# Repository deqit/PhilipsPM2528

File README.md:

# Reviving a Philips PM2528 Digital Multimeter
Picked up this vintage multimeter a while back. Half-functional, no manuals, and full of mystery. Perfect!

It’s built around an Intel 8035 microcontroller and packed with analog boards. There wasn’t a complete service manual anywhere, so I decided to dive in myself. This project's become a learning experience in hardware reverse engineering, firmware disassembly, and documentation.

Also see https://hackaday.io/project/203720-reviving-a-philips-pm2528-digital-multimeter

# The project
The goal of this project is fixing the multimeter. Well... maybe not really. In real life, the road towards that goal is much more interesting. And I'm documenting everything I found along the way.

In this repository you'll find:
- Original Philips-documentation (at least, what I could find, unfortunately in lo-res)
- Schematics (KiCad)
- PCB Layouts (KiCad)
- Schematic/PCB of a risercard, for testing the expansionboards
- Disassembled firmware, including annotations (Ghidra)
- A lot of documentation regarding relais-mapping, IO-expander-ports, etc.
- Detailed scope- and logic analyzer screenprints and capture-logs
- Deepdive: Explaination of how-everything-works
- etc.

Everything you find here is work-in-progress. It might be incomplete, and some parts may not be 100% accurate yet. If you spot something interesting or catch an error, feel free to drop me a message.

# The components
### Overview
- See [PM2528 Overview](/Deepdive/Overview/README.md "A very broad overview")
### Risercard
- See [PM2528 Risercard](/Deepdive/Risercard/README.md "A Risercard for testing the Expansionboards")
### ADC
- See [ADC Overview](/Deepdive/ADC/README.md "The ADC in more detail")
- See [ADC Control (Expansionboard N20)](/Deepdive/N20/README.md "ADC Control (Expansionboard N20)")
- See [ADC Analog (Expansionboard N21)](/Deepdive/N21/README.md "ADC Analog (Expansionboard N21)")

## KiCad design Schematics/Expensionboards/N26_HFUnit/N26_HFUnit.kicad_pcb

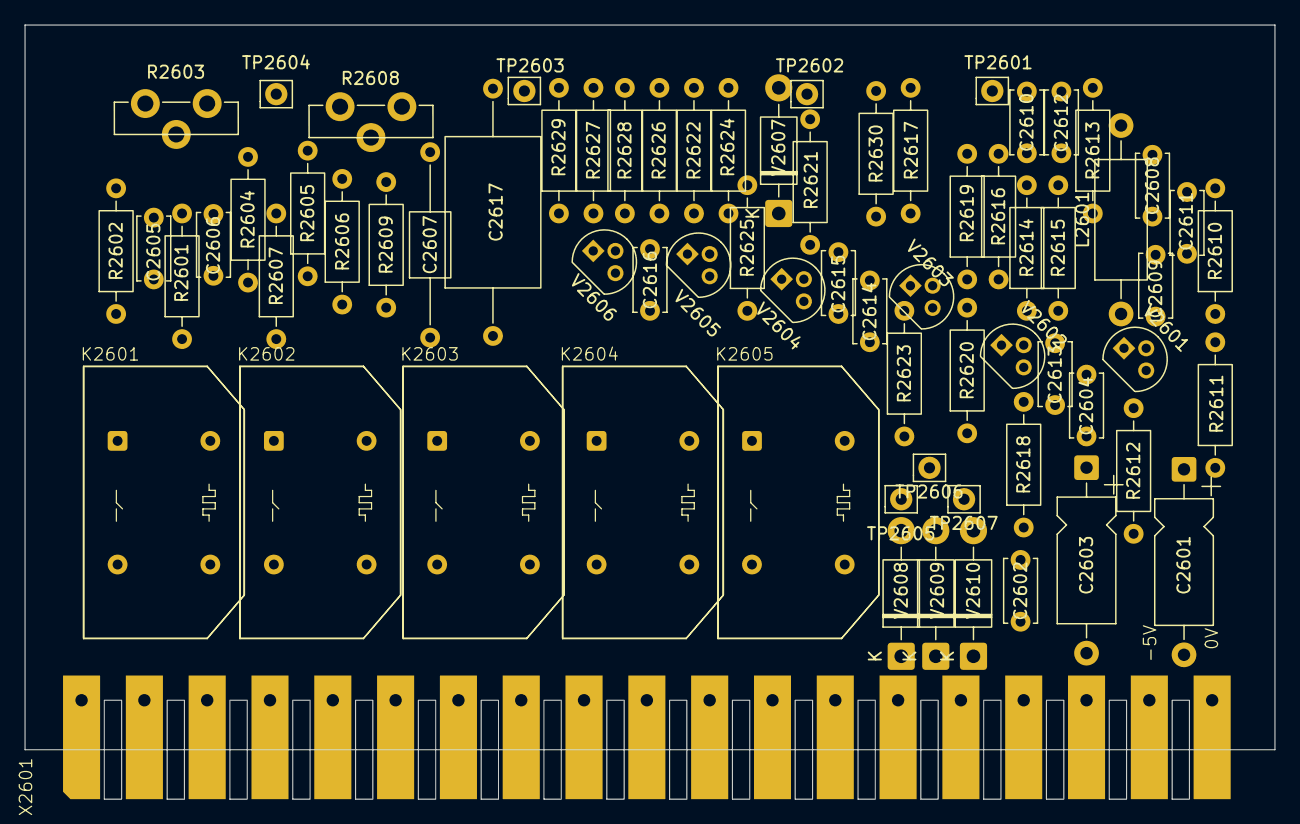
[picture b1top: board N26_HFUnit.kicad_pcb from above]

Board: 2 copper layers, 101.1 x 62.6 mm, 71 parts (0 on the bottom side), 40 nets, no tracks yet.

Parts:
C2601, C2603: 22u; CP_Axial_L10.0mm_D4.5mm_P15.00mm_Horizontal
C2602, C2604, C2610, C2611: 22n; C_Disc_D5.0mm_W2.5mm_P5.00mm
C2605, C2606, C2612, C2614, C2616: 10n; C_Disc_D5.0mm_W2.5mm_P5.00mm
C2607: 4n22; C_Axial_L5.1mm_D3.1mm_P15.00mm_Horizontal
C2608, C2609: 4n7; C_Disc_D5.0mm_W2.5mm_P5.00mm
C2613, C2615: 2n2; C_Disc_D5.0mm_W2.5mm_P5.00mm
C2617: 21n5; C_Axial_L12.0mm_D7.5mm_P20.00mm_Horizontal
K2601, K2602, K2603, K2604, K2605: Reed relay assy
L2601: 1m; L_Axial_L9.5mm_D4.0mm_P15.24mm_Horizontal_Fastron_SMCC
R2601: 4k02; R_Axial_DIN0207_L6.3mm_D2.5mm_P10.16mm_Horizontal
R2602, R2604, R2606: 1M; R_Axial_DIN0207_L6.3mm_D2.5mm_P10.16mm_Horizontal
R2603, R2608: 47k; Trimmer vertical
R2605: 10M; R_Axial_DIN0207_L6.3mm_D2.5mm_P10.16mm_Horizontal
R2607: 100; R_Axial_DIN0207_L6.3mm_D2.5mm_P10.16mm_Horizontal
R2609, R2622: 10k; R_Axial_DIN0207_L6.3mm_D2.5mm_P10.16mm_Horizontal
R2610: 8k25; R_Axial_DIN0207_L6.3mm_D2.5mm_P10.16mm_Horizontal
R2611: 27k4; R_Axial_DIN0207_L6.3mm_D2.5mm_P10.16mm_Horizontal
R2612: 3k83; R_Axial_DIN0207_L6.3mm_D2.5mm_P10.16mm_Horizontal
R2613: 33k2; R_Axial_DIN0207_L6.3mm_D2.5mm_P10.16mm_Horizontal
R2614: 68R1; R_Axial_DIN0207_L6.3mm_D2.5mm_P10.16mm_Horizontal
R2615: 4k64; R_Axial_DIN0207_L6.3mm_D2.5mm_P10.16mm_Horizontal
R2616, R2621: 5k62; R_Axial_DIN0207_L6.3mm_D2.5mm_P10.16mm_Horizontal
R2617: 12k1; R_Axial_DIN0207_L6.3mm_D2.5mm_P10.16mm_Horizontal
R2618, R2620, R2623, R2625, R2626: 15k4; R_Axial_DIN0207_L6.3mm_D2.5mm_P10.16mm_Horizontal
R2619, R2624: 178; R_Axial_DIN0207_L6.3mm_D2.5mm_P10.16mm_Horizontal
R2627, R2629: 154; R_Axial_DIN0207_L6.3mm_D2.5mm_P10.16mm_Horizontal
R2628, R2630: 2k26; R_Axial_DIN0207_L6.3mm_D2.5mm_P10.16mm_Horizontal
TP2601, TP2602, TP2603, TP2604, TP2605, TP2606, TP2607: TestPoint; Pin_D0.9mm_L10.0mm_W2.4mm_FlatFork
V2601, V2602, V2603, V2604, V2605, V2606: BC547B; TO-92
V2607: OA95; D_DO-41_SOD81_P10.16mm_Horizontal
V2608, V2609, V2610: BAX12A; D_DO-41_SOD81_P10.16mm_Horizontal
X2601: PM2528_RiserCardConnector

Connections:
+15V: C2601.1, C2602.1, C2608.1, C2611.1, L2601.1, R2608.3, R2610.2, R2617.2, R2622.2, R2627.2, X2601.4
+Vprobe: C2605.1, R2602.2, X2601.16
-15V: C2603.2, C2604.2, R2608.1, R2618.1, R2620.1, R2623.1, R2625.1, R2628.1, X2601.3
-Vprobe: C2606.2, R2604.1, X2601.15
/DCAmp: K2604.1, X2601.10
/DataholdA: K2603.1, X2601.12
/DataholdB: C2617.1, K2603.5, X2601.13
/LGND3: C2605.2, C2606.1, K2601.5, K2602.1, R2601.1, R2607.1, TP2604.1 (1_1), X2601.18
/LGND4: K2601.6, K2602.6, K2603.6, K2604.6, K2605.6, V2608.1 (K), V2609.1 (K), V2610.1 (K), X2601.19
/LGND5: C2601.2, C2602.2, C2603.1, C2604.1, C2611.2, C2613.1, C2615.1, R2611.1, R2612.1, R2614.1, R2619.1, R2624.1, R2626.1, V2607.1 (K), X2601.1 (0V_1)
/OCAmp: R2630.1, X2601.11
/Probe_0VA: K2602.5, X2601.14
/Probe_0VB: R2601.2, X2601.17
/REL2600A: K2601.10, TP2605.1 (1_1), V2608.2 (A), X2601.9
/REL2600B: K2602.10, K2603.10, TP2606.1 (1_1), V2609.2 (A), X2601.7
/REL2600C: K2604.10, K2605.10, TP2607.1 (1_1), V2610.2 (A), X2601.6
unnamed: C2607.1, R2603.2, R2605.2, R2609.1
unnamed: C2608.2, C2609.1, C2612.2, R2612.2, R2613.2
unnamed: C2609.2, L2601.2
unnamed: C2610.1, R2613.1, R2614.2
unnamed: C2610.2, TP2601.1 (1_1)
unnamed: C2612.1, R2615.2
unnamed: C2613.2, R2616.1
unnamed: C2614.1, R2623.2
unnamed: C2614.2, R2617.1
unnamed: C2615.2, R2621.1
unnamed: C2616.1, R2626.2
unnamed: C2616.2, R2622.1
unnamed: C2617.2, R2629.1, TP2603.1 (1_1)
unnamed: K2601.1, R2602.1, R2603.3
unnamed: K2604.5, R2609.2
unnamed: R2603.1, R2604.2
unnamed: R2605.1, R2606.2, R2607.2
unnamed: R2606.1, R2608.2
unnamed: R2610.1, R2611.2
unnamed: R2615.1, R2618.2
unnamed: R2619.2, R2620.2
unnamed: R2624.2, R2625.2
unnamed: R2628.2, R2629.2
unnamed: C2607.2, R2616.2, R2621.2, R2630.2, TP2602.1 (1_1), V2607.2 (A)

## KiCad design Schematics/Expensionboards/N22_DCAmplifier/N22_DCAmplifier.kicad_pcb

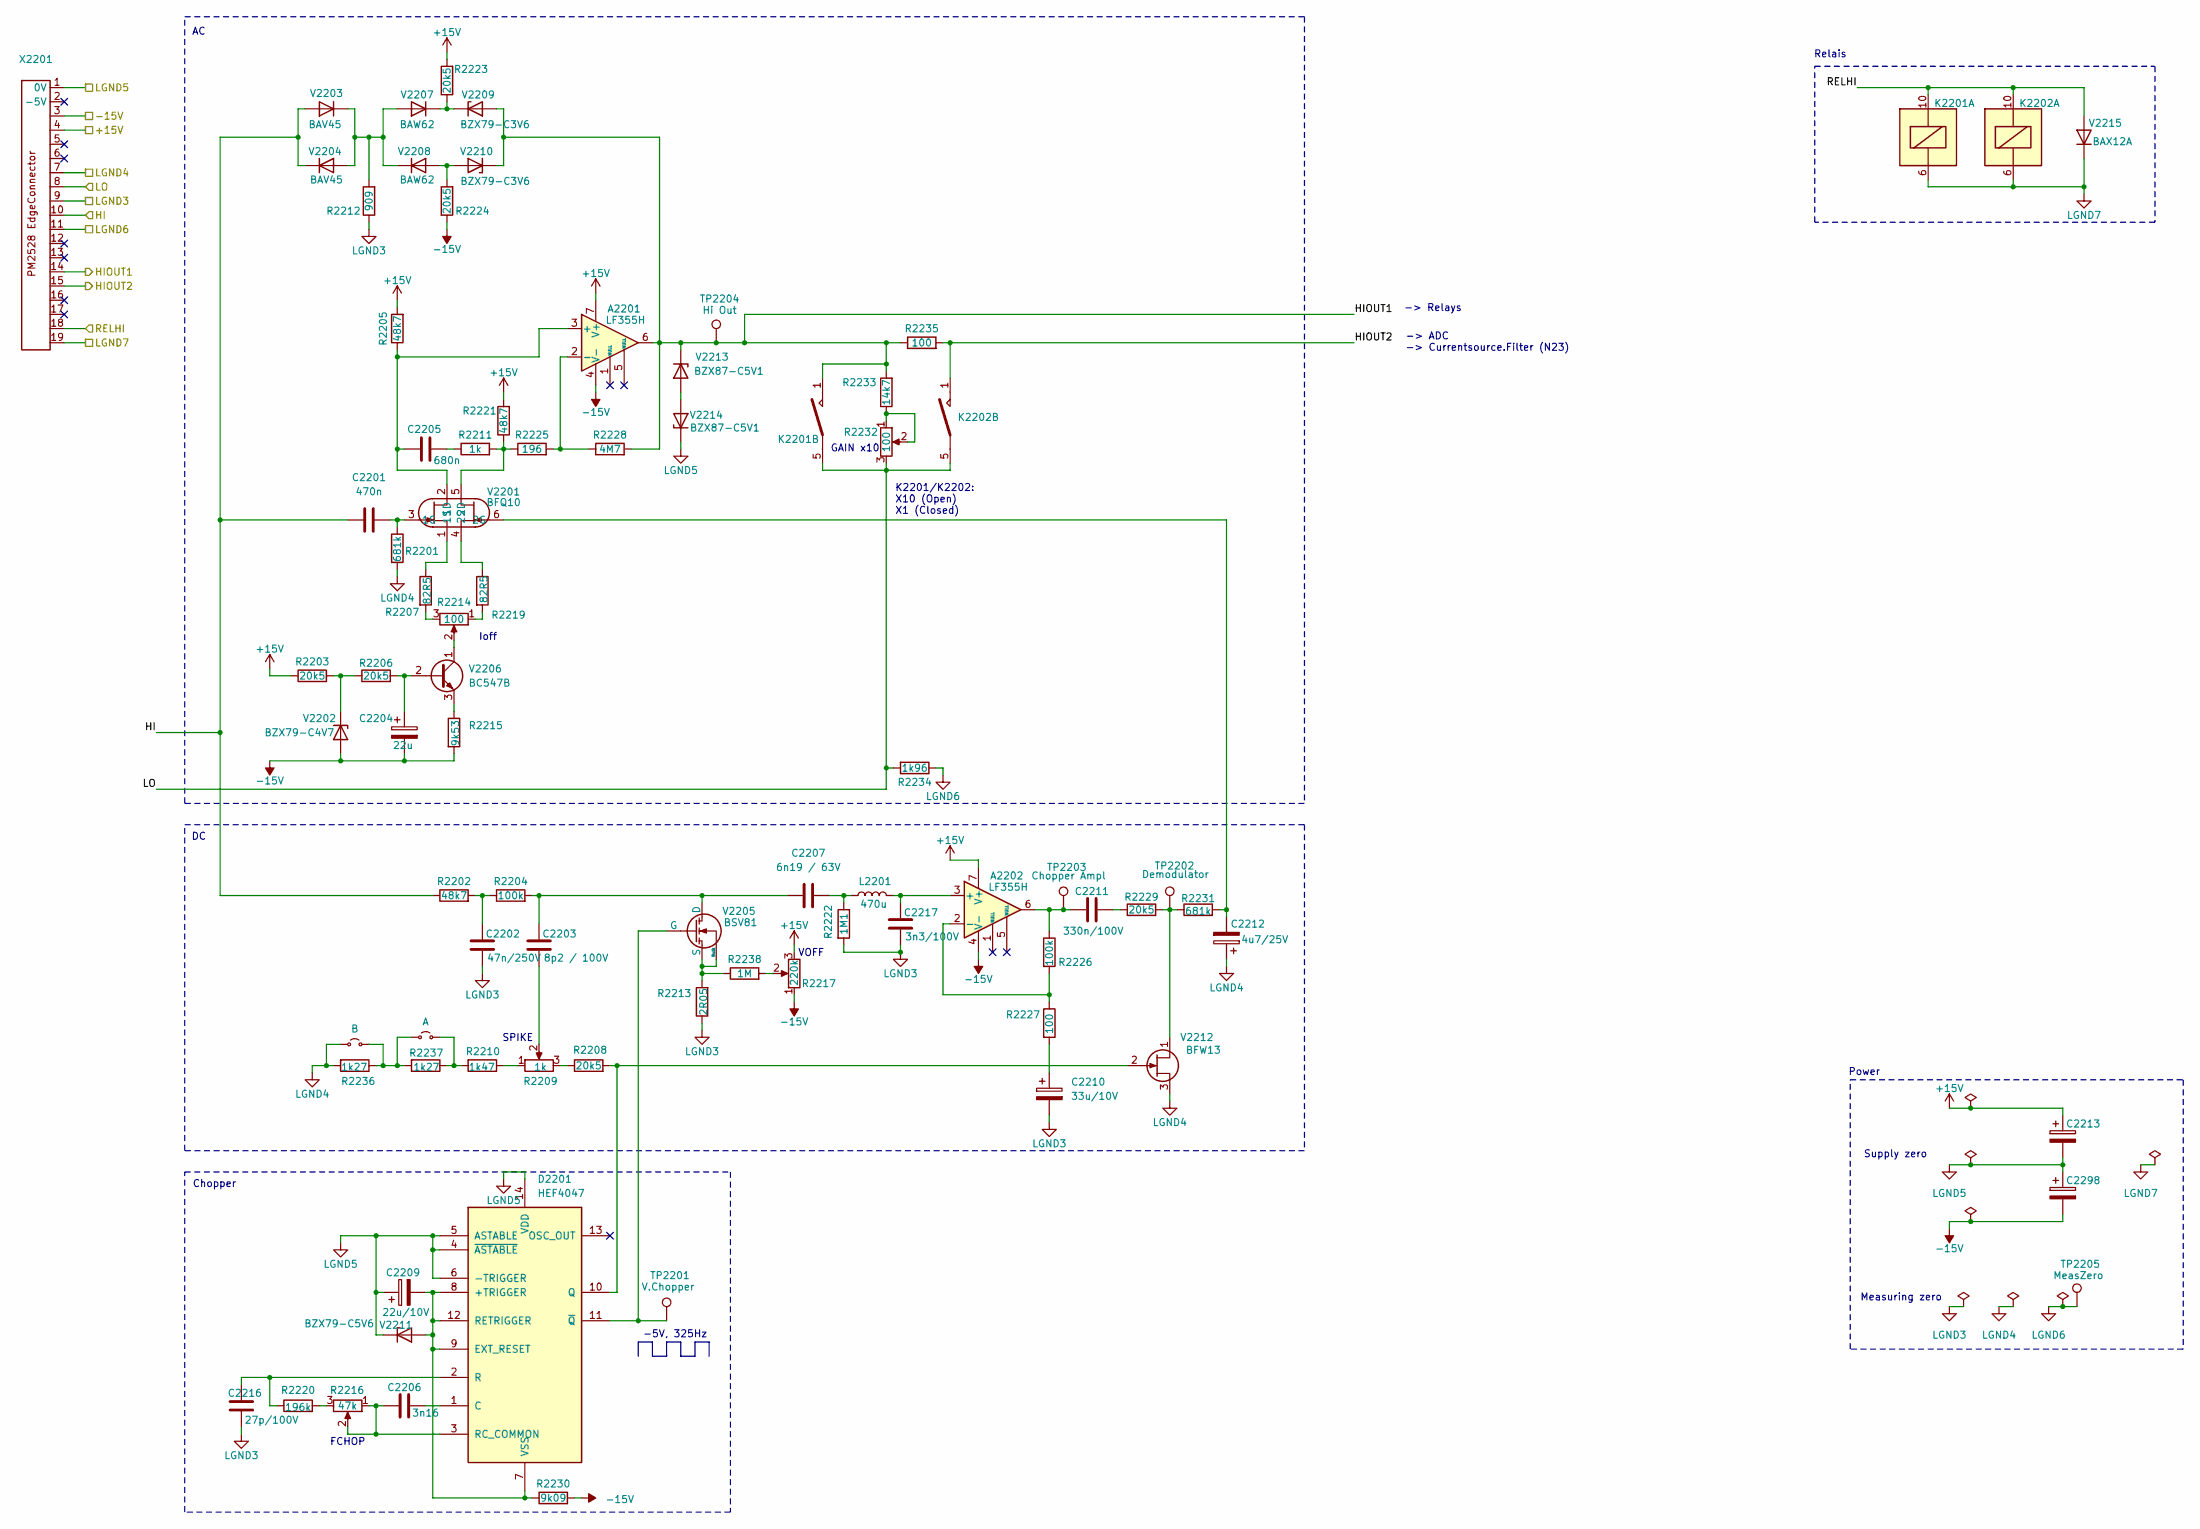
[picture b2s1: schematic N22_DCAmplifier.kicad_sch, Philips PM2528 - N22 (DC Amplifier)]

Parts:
A2201, A2202: LF355H; DIP-8_W7.62mm
C2201: 470n; C_Rect_L18.0mm_W6.0mm_P15.00mm_FKS3_FKP3
C2202: 47n/250V; C_Rect_L10.0mm_W4.0mm_P7.50mm_FKS3_FKP3
C2203: 8p2 / 100V; C_Disc_D4.3mm_W1.9mm_P5.00mm
C2204: 22u; CP_Radial_Tantal_D4.5mm_P5.00mm
C2205: 680n; C_Rect_L18.0mm_W5.0mm_P15.00mm_FKS3_FKP3
C2206: 3n16; C_Axial_L3.8mm_D2.6mm_P15.00mm_Horizontal
C2207: 6n19 / 63V; C_Axial_L3.8mm_D2.6mm_P15.00mm_Horizontal
C2209: 22u/10V; C_Disc_D5.0mm_W2.5mm_P5.00mm
C2210: 33u/10V; CP_Radial_Tantal_D4.5mm_P5.00mm
C2211: 330n/100V; C_Rect_L18.0mm_W5.0mm_P15.00mm_FKS3_FKP3
C2212: 4u7/25V; CP_Radial_Tantal_D4.5mm_P5.00mm
C2213, C2298: C_Polarized; C_Disc_D4.7mm_W2.5mm_P5.00mm
C2216: 27p/100V; C_Disc_D5.1mm_W3.2mm_P5.00mm
C2217: 3n3/100V; C_Disc_D4.3mm_W1.9mm_P5.00mm
D2201: HEF4047; DIP-14_W7.62mm
JP2201: A; TestPoint_Bridge_Pitch5.08mm_Drill0.7mm
JP2202: B; TestPoint_Bridge_Pitch5.08mm_Drill0.7mm
K2201, K2202: Reed relay assy
L2201: 470u; L_Axial_L9.5mm_D4.0mm_P15.24mm_Horizontal_Fastron_SMCC
R2201, R2231: 681k; R_Axial_DIN0207_L6.3mm_D2.5mm_P10.16mm_Horizontal
R2202, R2205, R2221: 48k7; R_Axial_DIN0207_L6.3mm_D2.5mm_P10.16mm_Horizontal
R2203, R2206, R2208, R2223, R2224, R2229: 20k5; R_Axial_DIN0207_L6.3mm_D2.5mm_P10.16mm_Horizontal
R2204, R2226: 100k; R_Axial_DIN0207_L6.3mm_D2.5mm_P10.16mm_Horizontal
R2207, R2219: 82R5; R_Axial_DIN0207_L6.3mm_D2.5mm_P10.16mm_Horizontal
R2209: 1k; Trimmer vertical
R2210: 1k47; R_Axial_DIN0207_L6.3mm_D2.5mm_P10.16mm_Horizontal
R2211: 1k; R_Axial_DIN0207_L6.3mm_D2.5mm_P10.16mm_Horizontal
R2212: 909; R_Axial_DIN0207_L6.3mm_D2.5mm_P10.16mm_Horizontal
R2213: 2R05; R_Axial_DIN0207_L6.3mm_D2.5mm_P10.16mm_Horizontal
R2214, R2232: 100; Trimmer vertical
R2215: 9k53; R_Axial_DIN0207_L6.3mm_D2.5mm_P10.16mm_Horizontal
R2216: 47k; Trimmer vertical
R2217: 220k; Trimmer vertical
R2220: 196k; R_Axial_DIN0207_L6.3mm_D2.5mm_P10.16mm_Horizontal
R2222: 1M1; R_Axial_DIN0207_L6.3mm_D2.5mm_P10.16mm_Horizontal
R2225: 196; R_Axial_DIN0207_L6.3mm_D2.5mm_P10.16mm_Horizontal
R2227, R2235: 100; R_Axial_DIN0207_L6.3mm_D2.5mm_P10.16mm_Horizontal
R2228: 4M7; R_Axial_DIN0207_L6.3mm_D2.5mm_P10.16mm_Horizontal
R2230: 9k09; R_Axial_DIN0207_L6.3mm_D2.5mm_P10.16mm_Horizontal
R2233: 14k7; R_Axial_DIN0207_L6.3mm_D2.5mm_P10.16mm_Horizontal
R2234: 1k96; R_Axial_DIN0207_L6.3mm_D2.5mm_P10.16mm_Horizontal
R2236, R2237: 1k27; R_Axial_DIN0207_L6.3mm_D2.5mm_P10.16mm_Horizontal
R2238: 1M; R_Axial_DIN0309_L9.0mm_D3.2mm_P12.70mm_Horizontal
TP2201: V.Chopper; Pin_D0.9mm_L10.0mm_W2.4mm_FlatFork
TP2202: Demodulator; Pin_D0.9mm_L10.0mm_W2.4mm_FlatFork
TP2203: Chopper Ampl; Pin_D0.9mm_L10.0mm_W2.4mm_FlatFork
TP2204: Hi Out; Pin_D0.9mm_L10.0mm_W2.4mm_FlatFork
TP2205: MeasZero; Pin_D0.9mm_L10.0mm_W2.4mm_FlatFork
V2201: BFQ10; TO-75-6
V2202: BZX79-C4V7; D_DO-35_SOD27_P10.16mm_Horizontal
V2203, V2204: BAV45; D_DO-35_SOD27_P7.62mm_Horizontal
V2205: BSV81; TO-72-4
V2206: BC547B; TO-92_Inline
V2207, V2208: BAW62; D_DO-35_SOD27_P10.16mm_Horizontal
V2209, V2210: BZX79-C3V6; D_DO-35_SOD27_P10.16mm_Horizontal
V2211: BZX79-C5V6; D_DO-35_SOD27_P10.16mm_Horizontal
V2212: BFW13; TO-72-4
V2213, V2214: BZX87-C5V1; D_DO-35_SOD27_P12.70mm_Horizontal
V2215: BAX12A; D_DO-35_SOD27_P10.16mm_Horizontal
X2201: PM2528_RiserCardConnector

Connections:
+15V: A2201.7 (V+), A2202.7 (V+), C2213.1, R2203.1, R2205.2, R2217.3, R2221.2, R2223.2, X2201.4
-15V: A2201.4 (V-), A2202.4 (V-), C2204.2, C2298.2, R2215.2, R2217.1, R2224.1, R2230.2, V2202.2 (A), X2201.3
/HI: C2201.1, R2202.1, V2203.2 (A), V2204.1 (K), X2201.10
/HIOUT1: A2201.6, K2201.1, R2228.2, R2233.2, R2235.1, TP2204.1 (1_1), V2209.2 (A), V2210.1 (K), V2213.1 (K), X2201.14
/HIOUT2: K2202.1, R2235.2, X2201.15
/LGND3: C2202.1, C2210.2, C2216.1, C2217.1, R2212.1, R2213.1, R2222.2, X2201.9
/LGND4: C2212.1, JP2202.1 (A_1), R2201.2, R2236.2, V2212.3 (S), X2201.7
/LGND5: C2209.1, C2213.2, C2298.1, D2201.4 (~ASTABLE), D2201.5 (ASTABLE), D2201.6 (-TRIGGER), D2201.14 (VDD), V2211.1 (K), V2214.1 (K), X2201.1 (0V_1)
/LGND6: R2234.1, TP2205.1 (1_1), X2201.11
/LGND7: K2201.6, K2202.6, V2215.1 (K), X2201.19
/LO: K2201.5, K2202.5, R2232.3, R2234.2, X2201.8
/RELHI: K2201.10, K2202.10, V2215.2 (A), X2201.18
unnamed: A2201.3 (+), C2205.1, R2205.1, V2201.2 (1D)
unnamed: A2201.2 (-), R2225.2, R2228.1
unnamed: A2202.3 (+), C2217.2, L2201.2
unnamed: A2202.2 (-), R2226.2, R2227.1
unnamed: A2202.6, C2211.1, R2226.1, TP2203.1 (1_1)
unnamed: C2202.2, R2202.2, R2204.1
unnamed: C2203.1, R2209.2
unnamed: C2205.2, R2211.1
unnamed: C2207.2, L2201.1, R2222.1
unnamed: C2210.1, R2227.2
unnamed: C2211.2, R2229.1
unnamed: C2209.2, D2201.7 (VSS), D2201.8 (+TRIGGER), D2201.9 (EXT_RESET), D2201.12 (RETRIGGER), R2230.1, V2211.2 (A)
unnamed: C2206.2, D2201.1 (C)
unnamed: D2201.10 (Q), R2208.2, V2212.2 (G)
unnamed: C2216.2, D2201.2 (R), R2220.1
unnamed: C2206.1, D2201.3 (RC_COMMON), R2216.1, R2216.2
unnamed: D2201.11 (~Q), TP2201.1 (1_1), V2205.2 (G)
unnamed: JP2201.1 (A_1), JP2202.2 (B), R2236.1, R2237.2
unnamed: JP2201.2 (B), R2210.2, R2237.1
unnamed: R2207.2, R2214.3
unnamed: R2208.1, R2209.3
unnamed: R2209.1, R2210.1
unnamed: R2214.1, R2219.2
unnamed: R2216.3, R2220.2
unnamed: R2217.2, R2238.2
unnamed: R2232.1, R2232.2, R2233.1
unnamed: C2201.2, R2201.1, V2201.3 (1G)
unnamed: R2207.1, V2201.1 (1S)
unnamed: R2211.2, R2221.1, R2225.1, V2201.5 (2D)
unnamed: C2212.2, R2231.2, V2201.6 (2G)
unnamed: R2219.1, V2201.4 (2S)
unnamed: R2203.2, R2206.1, V2202.1 (K)
unnamed: R2212.2, V2203.1 (K), V2204.2 (A), V2207.2 (A), V2208.1 (K)
unnamed: R2213.2, R2238.1, V2205.3 (S), V2205.4 (Bulk)
unnamed: C2203.2, C2207.1, R2204.2, V2205.1 (D)
unnamed: C2204.1, R2206.2, V2206.2 (B)
unnamed: R2214.2, V2206.1 (C)
unnamed: R2215.1, V2206.3 (E)
unnamed: R2223.1, V2207.1 (K), V2209.1 (K)
unnamed: R2224.2, V2208.2 (A), V2210.2 (A)
unnamed: R2229.2, R2231.1, TP2202.1 (1_1), V2212.1 (D)
unnamed: V2213.2 (A), V2214.2 (A)

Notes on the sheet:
-> Relays
Relais
-> ADC -> Currentsource.Filter (N23)
FCHOP
SPIKE
Supply zero
GAIN x10
K2201/K2202: X10 (Open) X1 (Closed)
VOFF
Chopper
-5V, 325Hz
Power
Measuring zero
Ioff

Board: 2 copper layers, 81 parts (0 on the bottom side), 54 nets, no tracks yet.

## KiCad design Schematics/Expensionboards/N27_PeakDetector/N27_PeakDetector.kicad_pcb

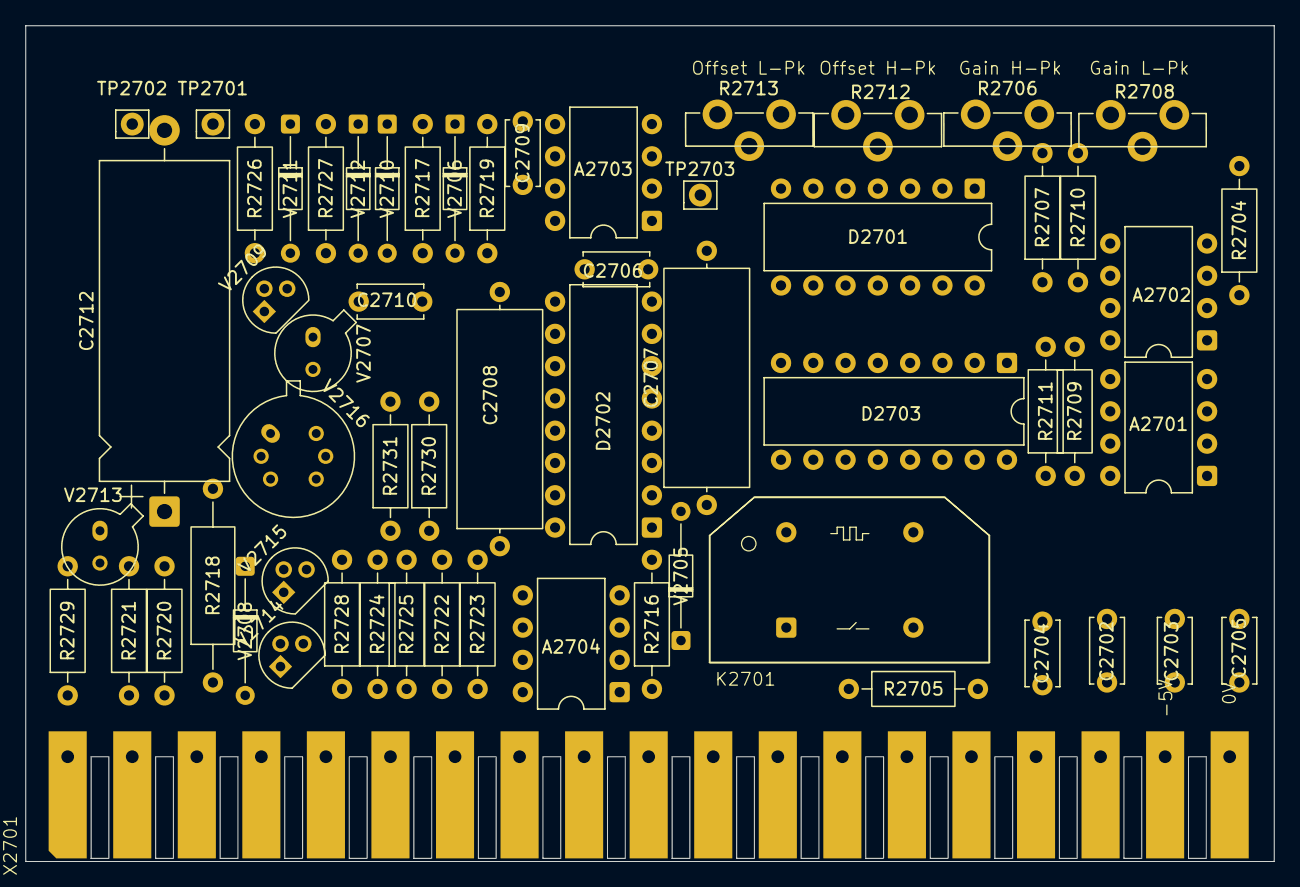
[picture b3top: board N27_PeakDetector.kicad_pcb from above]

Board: 2 copper layers, 98.2 x 65.8 mm, 60 parts (0 on the bottom side), 46 nets, no tracks yet.

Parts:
A2701, A2702, A2704: LF355H; DIP-8_W7.62mm
A2703: LM315; DIP-8_W7.62mm
C2702, C2703: 6u8; C_Disc_D5.0mm_W2.5mm_P5.00mm
C2704, C2705: 22u; C_Disc_D5.0mm_W2.5mm_P5.00mm
C2706, C2709, C2710: 2u2; C_Disc_D5.0mm_W2.5mm_P5.00mm
C2707: 680n; C_Axial_L17.0mm_D6.5mm_P20.00mm_Horizontal
C2708: 220n; C_Axial_L17.0mm_D6.5mm_P20.00mm_Horizontal
C2712: 162n; CP_Axial_L25.0mm_D10.0mm_P30.00mm_Horizontal
D2701: HEF4066; DIP-14_W7.62mm
D2702: HEF4528; DIP-16_W7.62mm
D2703: HEF4104; DIP-16_W7.62mm
K2701: Reed relay assy
R2704: 10k1; R_Axial_DIN0207_L6.3mm_D2.5mm_P10.16mm_Horizontal
R2705: 90k9; R_Axial_DIN0207_L6.3mm_D2.5mm_P10.16mm_Horizontal
R2706: 330; Trimmer vertical
R2707: 36k5; R_Axial_DIN0207_L6.3mm_D2.5mm_P10.16mm_Horizontal
R2708: 100; Trimmer vertical
R2709, R2711: 1k; R_Axial_DIN0207_L6.3mm_D2.5mm_P10.16mm_Horizontal
R2710: 10k; R_Axial_DIN0207_L6.3mm_D2.5mm_P10.16mm_Horizontal
R2712, R2713: 22k; Trimmer vertical
R2716: 1M8; R_Axial_DIN0207_L6.3mm_D2.5mm_P10.16mm_Horizontal
R2717: 1M1; R_Axial_DIN0207_L6.3mm_D2.5mm_P10.16mm_Horizontal
R2718: 33M; R_Axial_DIN0309_L9.0mm_D3.2mm_P15.24mm_Horizontal
R2719: 100k; R_Axial_DIN0207_L6.3mm_D2.5mm_P10.16mm_Horizontal
R2720: 226k; R_Axial_DIN0207_L6.3mm_D2.5mm_P10.16mm_Horizontal
R2721: 287; R_Axial_DIN0207_L6.3mm_D2.5mm_P10.16mm_Horizontal
R2722, R2723: 5k62; R_Axial_DIN0207_L6.3mm_D2.5mm_P10.16mm_Horizontal
R2724, R2730, R2731: 48k7; R_Axial_DIN0207_L6.3mm_D2.5mm_P10.16mm_Horizontal
R2725: 105k; R_Axial_DIN0207_L6.3mm_D2.5mm_P10.16mm_Horizontal
R2726: 4k87; R_Axial_DIN0207_L6.3mm_D2.5mm_P10.16mm_Horizontal
R2727: 3k83; R_Axial_DIN0207_L6.3mm_D2.5mm_P10.16mm_Horizontal
R2728: 22R6; R_Axial_DIN0207_L6.3mm_D2.5mm_P10.16mm_Horizontal
R2729: 22k6; R_Axial_DIN0207_L6.3mm_D2.5mm_P10.16mm_Horizontal
TP2701, TP2703: Pin_D0.9mm_L10.0mm_W2.4mm_FlatFork
TP2702: MeasZero; Pin_D0.9mm_L10.0mm_W2.4mm_FlatFork
V2705: BAX12; D_DO-34_SOD68_P10.16mm_Horizontal
V2706, V2708, V2710: BAW62; D_DO-34_SOD68_P10.16mm_Horizontal
V2707, V2713: BAV45; TO-18-2
V2709, V2715: BC559; TO-92
V2711: BZX79-6V2; D_DO-34_SOD68_P10.16mm_Horizontal
V2712: BZX79-3V6; D_DO-34_SOD68_P10.16mm_Horizontal
V2714: BC547; TO-92
V2716: ON528; TO-5-6
X2701: PM2528_RiserCardConnector

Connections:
+5V: C2704.1, D2701.14 (VDD), D2703.1 (Vddo), X2701.5
+15V: A2701.7 (V+), A2702.7 (V+), A2703.8 (V+), A2704.7 (V+), C2702.1, C2710.1, R2712.2, R2713.2, R2726.2, R2729.2, V2711.1 (K), V2716.2 (D), V2716.5 (D), X2701.4
-5V: A2703.1 (GND), C2705.2, C2706.2, D2701.3, D2701.4, D2701.5, D2701.7 (VSS), D2701.10, D2701.11, D2701.12, D2702.4 (B), D2702.8 (VSS), D2702.12 (B), D2703.8 (Vss), R2725.1, X2701.2 (-5V)
-15V: A2701.4 (V-), A2702.4 (V-), A2703.4 (V-), A2704.4 (V-), C2703.2, C2709.2, R2720.1, R2730.1, R2731.1, X2701.3
/IN: K2701.5, R2705.1, X2701.7
/OUT: A2703.3 (-), A2704.6, R2721.2, TP2703.1 (1_1), V2716.6 (G), X2701.12
/SEL_UD: D2703.4, X2701.11
/X10: K2701.10, V2705.2 (A), X2701.9
//BSY: D2702.7 (Q), X2701.15
//RESET: R2722.1, X2701.14
//STADC: D2702.9 (Q), X2701.16
GND1: A2702.3 (+), C2702.2, C2703.1, C2704.2, C2705.1, C2712.2, R2707.1, R2717.2, TP2702.1 (1_1), X2701.6, X2701.8, X2701.19
GND2: C2706.1, C2709.1, C2710.2, D2702.3 (R), D2702.13 (R), D2702.16 (VDD), D2703.5, D2703.11, D2703.12, D2703.15 (EN), D2703.16 (Vddi), K2701.6, R2716.2, R2723.1, V2705.1 (K), V2708.2 (A), V2712.2 (A), X2701.1 (0V), X2701.10
unnamed: A2701.3 (+), K2701.1, R2704.1, R2705.2
unnamed: A2701.2 (-), R2708.2
unnamed: A2701.1 (NULL), R2713.3
unnamed: A2701.5 (NULL), R2713.1
unnamed: A2701.6, R2708.3, R2709.1
unnamed: A2702.2 (-), R2704.2, R2706.3
unnamed: A2702.1 (NULL), R2712.3
unnamed: A2702.5 (NULL), R2712.1
unnamed: A2702.6, R2710.2, R2711.1
unnamed: A2703.2 (+), D2701.2, D2701.9, TP2701.1 (1_1)
unnamed: A2704.3 (+), R2730.2, V2716.1 (S)
unnamed: A2704.2 (-), R2731.2, V2716.4 (S)
unnamed: D2701.6, D2703.3
unnamed: D2701.13, D2703.2
unnamed: D2702.5 (A), R2719.1
unnamed: C2707.2, D2702.1 (CX)
unnamed: C2707.1, D2702.2 (Rx), R2716.1
unnamed: D2702.6 (Q), D2702.11 (A)
unnamed: C2708.2, D2702.15 (CX)
unnamed: C2708.1, D2702.14 (Rx), R2717.1
unnamed: R2706.1, R2706.2, R2710.1
unnamed: R2707.2, R2708.1
unnamed: R2718.2, R2720.2, R2721.1
unnamed: R2722.2, R2723.2
unnamed: R2724.2, R2725.2
unnamed: V2706.2 (A), V2707.2 (A), V2710.2 (A)
unnamed: A2703.7, R2719.2, V2706.1 (K)
unnamed: C2712.1, R2718.1, V2707.1 (K), V2713.2 (A), V2716.3 (G)
unnamed: R2727.1, V2710.1 (K), V2712.1 (K)
unnamed: R2727.2, V2711.2 (A)
unnamed: R2728.2, R2729.1, V2713.1 (K)
unnamed: D2701.8, R2709.2
unnamed: D2701.1, R2711.2

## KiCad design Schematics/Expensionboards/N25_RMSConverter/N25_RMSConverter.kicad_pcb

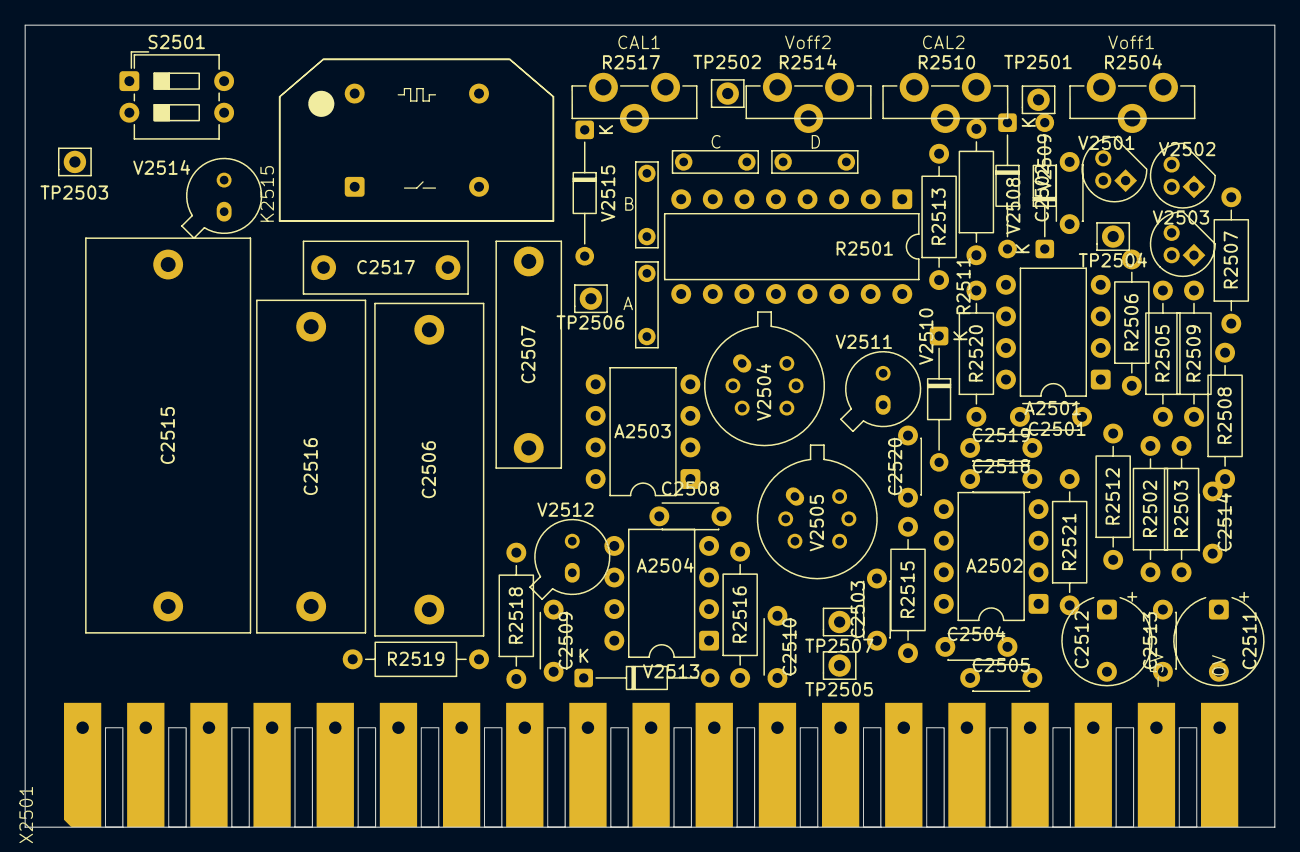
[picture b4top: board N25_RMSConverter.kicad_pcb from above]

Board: 2 copper layers, 100.5 x 64.5 mm, 72 parts (0 on the bottom side), 48 nets, no tracks yet.

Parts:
A2501, A2503, A2504: LM308AN; DIP-8_W7.62mm
A2502: LF356BN; DIP-8_W7.62mm
C2501: 22p; C_Disc_D4.3mm_W1.9mm_P5.00mm
C2502, C2510: 470p; C_Disc_D4.3mm_W1.9mm_P5.00mm
C2503, C2509: 100p; C_Disc_D4.3mm_W1.9mm_P5.00mm
C2504, C2505, C2518: 10n; C_Disc_D4.3mm_W1.9mm_P5.00mm
C2506: 3u3; C_Rect_L26.5mm_W8.5mm_P22.50mm_MKS4
C2507: 330n; C_Rect_L18.0mm_W5.0mm_P15.00mm_FKS3_FKP3
C2508: 10p; C_Disc_D4.3mm_W1.9mm_P5.00mm
C2511, C2512: 6u8; CP_Radial_Tantal_D7.0mm_P5.00mm
C2513, C2514: 22n; C_Disc_D4.3mm_W1.9mm_P5.00mm
C2515: 6u8; C_Rect_L31.5mm_W13.0mm_P27.50mm_MKS4
C2516: 2u2; C_Rect_L26.5mm_W8.5mm_P22.50mm_MKS4
C2517: 100n; C_Rect_L13.0mm_W4.0mm_P10.00mm_FKS3_FKP3_MKS4
C2519: 2n2; C_Disc_D4.3mm_W1.9mm_P5.00mm
C2520: 18p; C_Disc_D4.3mm_W1.9mm_P5.00mm
JP2501: A; TestPoint_Bridge_Pitch5.08mm_Drill0.7mm
JP2502: B; TestPoint_Bridge_Pitch5.08mm_Drill0.7mm
JP2503: C; TestPoint_Bridge_Pitch5.08mm_Drill0.7mm
JP2504: D; TestPoint_Bridge_Pitch5.08mm_Drill0.7mm
K2515: Reed relay assy
R2501: OM529; DIP-16_W7.62mm
R2502: 19R6; R_Axial_DIN0207_L6.3mm_D2.5mm_P10.16mm_Horizontal
R2503, R2513: 301k; R_Axial_DIN0207_L6.3mm_D2.5mm_P10.16mm_Horizontal
R2504, R2514: 47k; Trimmer vertical
R2505: 750; R_Axial_DIN0207_L6.3mm_D2.5mm_P10.16mm_Horizontal
R2506: 590; R_Axial_DIN0207_L6.3mm_D2.5mm_P10.16mm_Horizontal
R2507: 301; R_Axial_DIN0207_L6.3mm_D2.5mm_P10.16mm_Horizontal
R2508: 7k87; R_Axial_DIN0207_L6.3mm_D2.5mm_P10.16mm_Horizontal
R2509: 1k96; R_Axial_DIN0207_L6.3mm_D2.5mm_P10.16mm_Horizontal
R2510: 1K; Trimmer vertical
R2511: 8R25; R_Axial_DIN0207_L6.3mm_D2.5mm_P10.16mm_Horizontal
R2512: 115; R_Axial_DIN0207_L6.3mm_D2.5mm_P10.16mm_Horizontal
R2515, R2518: 2k05; R_Axial_DIN0207_L6.3mm_D2.5mm_P10.16mm_Horizontal
R2516: 4k02; R_Axial_DIN0207_L6.3mm_D2.5mm_P10.16mm_Horizontal
R2517: 330; Trimmer vertical
R2519: 3k01; R_Axial_DIN0207_L6.3mm_D2.5mm_P10.16mm_Horizontal
R2520: 5M6; R_Axial_DIN0207_L6.3mm_D2.5mm_P10.16mm_Horizontal
R2521: 33M; R_Axial_DIN0207_L6.3mm_D2.5mm_P10.16mm_Horizontal
S2501: SW_DPST_x2; SW_DIP_SPSTx02_Slide_6.7x6.64mm_W7.62mm_P2.54mm_LowProfile
TP2501, TP2502, TP2504, TP2507: Pin_D0.9mm_L10.0mm_W2.4mm_FlatFork
TP2503: OUT; Pin_D0.9mm_L10.0mm_W2.4mm_FlatFork
TP2505: IN; Pin_D0.9mm_L10.0mm_W2.4mm_FlatFork
TP2506: 0V; Pin_D0.9mm_L10.0mm_W2.4mm_FlatFork
V2501, V2502: BC547B; TO-92
V2503: BC559B; TO-92
V2504, V2505: MAT01GH; TO-78-6
V2508, V2509, V2513: BAW62; D_DO-34_SOD68_P10.16mm_Horizontal
V2510: BZX79-B4V7; D_DO-34_SOD68_P10.16mm_Horizontal
V2511, V2512, V2514: BAV45; TO-18-2
V2515: BAX12A; D_DO-34_SOD68_P10.16mm_Horizontal
X2501: PM2528_RiserCardConnector

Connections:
+5V: R2518.2, X2501.5
+15V: A2501.7 (V+), A2502.7 (V+), A2503.7 (V+), A2504.7 (V+), C2504.1, C2511.1, C2513.1, R2504.1, R2505.2, R2506.2, R2514.1, X2501.4
-15V: A2501.4 (V-), A2502.4 (V-), A2503.4 (V-), A2504.4 (V-), C2505.2, C2512.2, C2514.2, R2504.3, R2507.1, R2509.1, R2514.3, V2510.2 (A), X2501.3
/D1703.22: K2515.10, V2515.2 (A), X2501.15
/IN: C2518.2, R2501.16, R2521.1, TP2505.1 (1_1), X2501.7
/OUT: C2516.2, C2517.2, R2501.10, TP2503.1 (1_1), V2514.2 (A), X2501.13
GND3: C2504.2, C2505.1, C2511.2, C2512.1, C2513.2, C2514.1, R2508.1, R2519.1, TP2506.1 (1_1), X2501.1 (0V_1)
GND4: A2503.3 (+), A2504.3 (+), R2502.1, R2512.1, V2504.2 (B), V2504.5 (B), X2501.8, X2501.12
GND5: C2509.2, C2517.1, K2515.5, S2501.3 (A), X2501.11
GND6: K2515.6, V2515.1 (K), X2501.14
unnamed: A2501.3 (+), R2502.2, R2503.2
unnamed: A2501.2 (-), C2502.2, R2510.2, TP2501.1 (1_1)
unnamed: A2501.1 (CompenA), C2501.2
unnamed: A2501.8 (CompenB), C2501.1
unnamed: A2502.3 (+), R2512.2, R2513.2
unnamed: A2502.2 (-), C2519.2, C2520.1, R2501.15, V2504.1 (C), V2511.1 (K)
unnamed: A2503.2 (-), C2506.1, C2507.1, R2501.13, V2505.6 (C)
unnamed: A2503.1 (CompenA), C2508.2
unnamed: A2503.8 (CompenB), C2508.1
unnamed: A2504.2 (-), C2510.2, R2517.1, R2517.2, V2504.6 (C), V2512.1 (K)
unnamed: A2504.8 (CompenB), C2509.1
unnamed: C2515.2, R2501.11
unnamed: C2518.1, R2520.2
unnamed: C2519.1, R2521.2
unnamed: JP2501.1 (A_1), R2501.8, R2517.3
unnamed: JP2502.1 (A_1), R2501.7
unnamed: JP2503.1 (A_1), R2501.6
unnamed: JP2504.1 (A_1), R2501.5
unnamed: K2515.1, R2501.9
unnamed: R2501.1, R2510.3, R2511.1, R2520.1
unnamed: R2501.3, R2510.1, R2511.2
unnamed: R2503.1, R2504.2
unnamed: R2513.1, R2514.2
unnamed: C2506.2, S2501.1 (A)
unnamed: A2503.6, C2507.2, R2501.12, S2501.2 (B), TP2502.1 (1_1)
unnamed: C2515.1, C2516.1, S2501.4 (B)
unnamed: A2501.6, V2510.1 (K)
unnamed: C2502.1, R2508.2, R2509.2
unnamed: V2508.2 (A), V2509.1 (K)
unnamed: V2504.3 (E), V2505.1 (C), V2505.2 (B)
unnamed: V2504.4 (E), V2505.5 (B), V2513.2 (A)
unnamed: C2503.2, R2515.2, TP2507.1 (1_1), V2505.3 (E), V2505.4 (E)
unnamed: R2501.14, TP2504.1 (1_1), V2508.1 (K)
unnamed: R2501.2, V2509.2 (A)
unnamed: A2502.6, C2503.1, C2520.2, R2515.1, V2511.2 (A)
unnamed: A2504.6, C2510.1, R2516.2, V2512.2 (A)
unnamed: R2516.1, V2513.1 (K)
unnamed: R2518.1, R2519.2, V2514.1 (K)
